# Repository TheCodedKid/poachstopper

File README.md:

<div align="center">

**Inline soft-start for Mini Cheetah motor controllers.**
Stops the power-on inrush surge that kills the input caps.

</div>

---

## Why

Cheap MIT Mini Cheetah clones have undersized input caps and no inrush limiting. Hot-plugging a charged battery, current spike into the FETs, caps die. No good, dead cheetah.

Poach Stopper splices inline on the battery lead, pre-charges through a resistor, then hands over full current. No MCU, no firmware, no buttons.

Delay time is calculated to be about `0.24` seconds, but this is due to nearly zero documentation on the knockoff motor's cap bank size, so this is more of a safety number + I think you can wait a quarter second, but if this is not the case, submit an issue.

## How it works

| Block | Parts | Job |
|-------|-------|-----|
| Soft-start bypass | G2RL-1A relay + R3 (10 Ω 5 W) | limits inrush; relay shorts it once charged |
| Delay timer | NE555 monostable mode |
| 5 V rail | LMR16006 buck, 24 V → 5 V | Powers the 555 + relay coil off the pack |
| Protection | Blade fuse F1, 1N4007 flyback D3 | Fault current + coil kickback |

<div align="center">

</div>

## Build it

JLCPCB order files are in `fab/`:

- `fab/poachstopper-gerbers.zip` — gerbers
- `fab/poachstopper-cpl.csv` — pick-and-place
- `bom/jlcpcb_bom.csv` — assembly BOM (LCSC parts)

**Hand-solder yourself** (not on PnP BOM): R3 (10 Ω 5 W), F1 fuse holder, RLA1 relay, XT60 connectors J1/J2.

Source is KiCad 10 — open `poachstopper.kicad_pro`.

## License

[MIT](LICENSE) © 2026 TheCodedKid

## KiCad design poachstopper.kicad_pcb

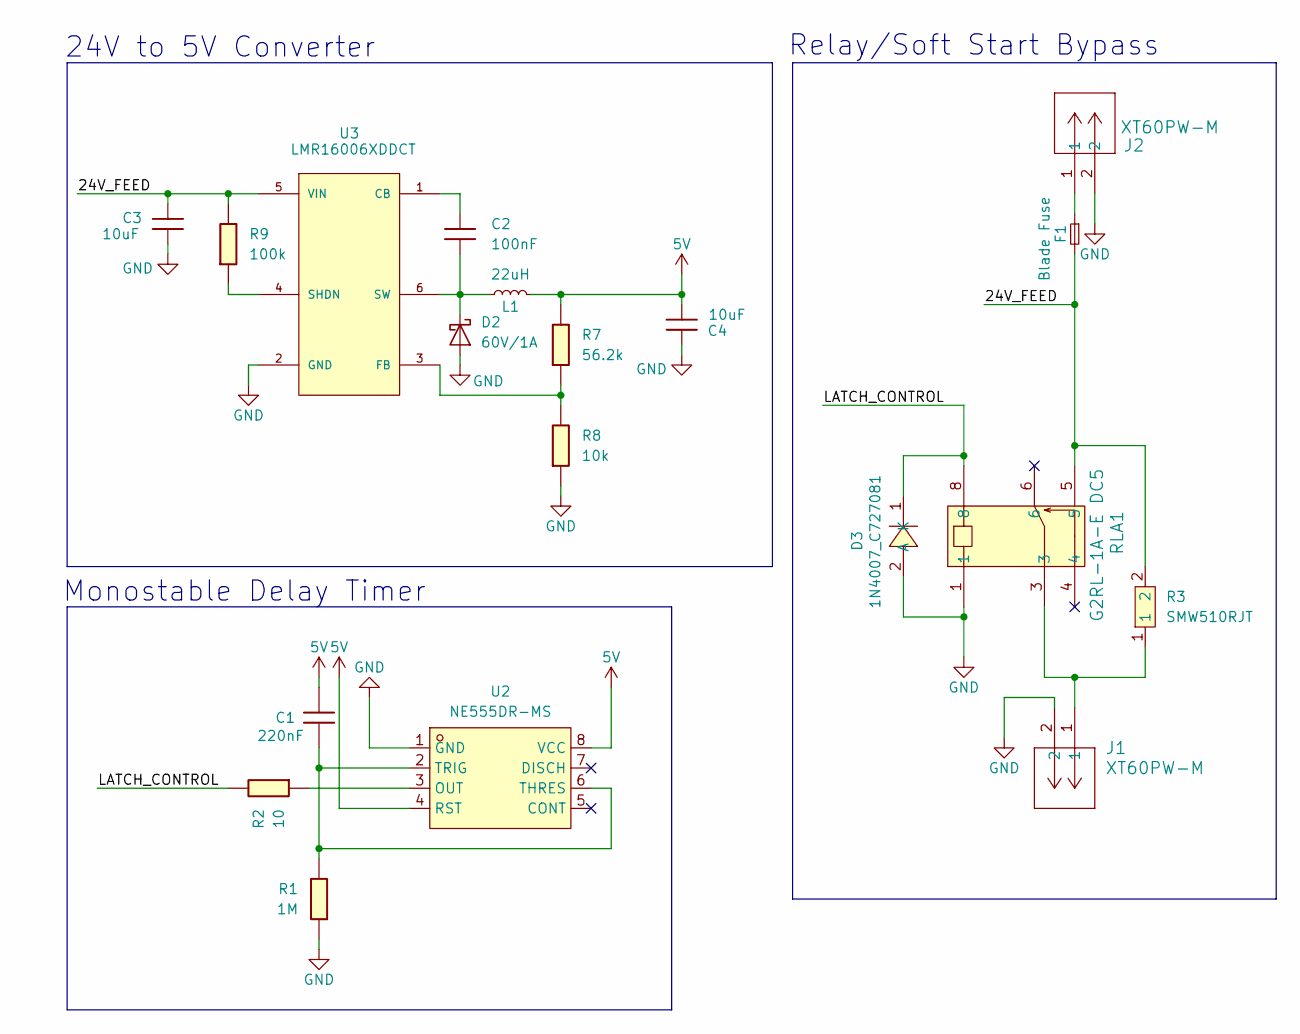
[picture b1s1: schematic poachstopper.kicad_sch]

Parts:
C1: 220nF; C_1206
C2: 100nF; C_1206
C3, C4: 10uF; C_1206
D2: 60V/1A; Diode_Schottky_0603
D3: 1N4007_C727081; SMA_L4.3-W2.5-LS5.0-RD; MPN 1N4007; LCSC Part C727081
F1: Blade Fuse; Fuseholder_Automotive
J1, J2: XT60PW-M; CONN_XT60PW-M_AMA
L1: 22uH; 0805
R1: 1M; R_1206
R2: 10; R_1206
R3: SMW510RJT; RES-SMD_L13.5-W7.3; MPN SMW510RJT; LCSC Part C2094091
R7: 56.2k; R_1206
R8: 10k; R_1206
R9: 100k; R_1206
RLA1: G2RL-1A-E DC5; RELAY_G2RL-1A-E_DC5_OMR
U2: NE555DR-MS; SOIC-8_L4.9-W3.9-P1.27-LS6.0-BL; MPN NE555DR-MS; LCSC Part C7434189
U3: LMR16006XDDCT; SOT95P280X110-6N

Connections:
5V: C1.1, C4.2, L1.2, R7.1, U2.4 (RST), U2.8 (VCC)
/24V_FEED: C3.1, F1.2, R3.2, R9.1, RLA1.5, U3.5 (VIN)
/LATCH_CONTROL: D3.1 (K), R2.1, RLA1.8
GND: C3.2, C4.1, D2.2 (A), D3.2 (A), J1.2, J2.2, R1.2, R8.2, RLA1.1, U2.1 (GND), U3.2 (GND)
unnamed: C2.2, D2.1 (K), L1.1, U3.6 (SW)
unnamed: F1.1, J2.1
unnamed: J1.1, R3.1, RLA1.3
unnamed: R2.2, U2.3 (OUT)
unnamed: C1.2, R1.1, U2.2 (TRIG), U2.6 (THRES)
unnamed: C2.1, U3.1 (CB)
unnamed: R7.2, R8.1, U3.3 (FB)
unnamed: R9.2, U3.4 (SHDN)

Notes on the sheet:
24V to 5V Converter
Relay/Soft Start Bypass
Monostable Delay Timer

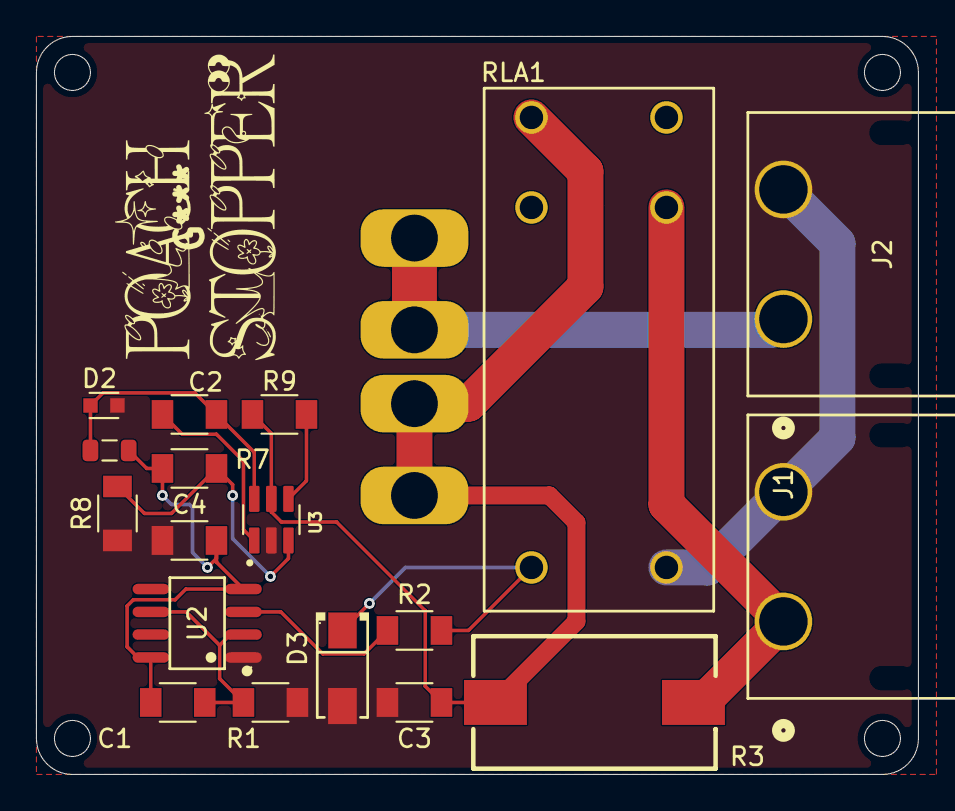
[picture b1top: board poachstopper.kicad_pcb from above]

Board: 2 copper layers, 49.0 x 41.0 mm, 19 parts (0 on the bottom side), 12 nets.

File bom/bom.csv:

Reference,Qty,Value,Footprint,MPN,Manufacturer,LCSC,LC_Stock,Chosen_Distributor,Datasheet,Validated,DNP,Notes
C1,1,220nF,1206,,,C107186,,,https://www.yageo.com/upload/media/product/productsearch/dat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,,,
D2,1,60V/1A,Diode_Schottky_0603,,,C3759853,,,https://www.digikey.com/en/products/detail/bourns-inc/CD0603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,,,
D3,1,1N4007,SMA_L4.3-W2.5-LS5.0-RD,1N4007,TWGMC(迪嘉),C727081,,,https://lcsc.com/product-detail/Diodes-General-Purpose_TWGMC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,,,SMD swap (SMA/DO-214AC) - change footprint from DO-41 before fab
F1,1,Blade Fuse,Fuseholder_Automotive,,,,,,https://www.keyelco.com/userAssets/file/M65p41.pdf,,yes,"Hand-solder, exclude from JLCPCB pick-and-place (DNP)"
"J1,J2",2,XT60PW-M,CONN_XT60PW-M_AMA,,,,,,XT60PW-M,,yes,"XT60 - order + solder separately, exclude from JLCPCB PnP (DNP)"
L1,1,22uH,0805,,,C6364733,,,https://mm.digikey.com/Volume0/opasdata/d220001/medias/docus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,,,
R1,1,1M,1206,,,C17927,,,,,,
R2,1,10,1206,,,C17903,,,,,,
R3,1,10,RES-SMD_L13.5-W7.3,SMW510RJT,TE Connectivity(泰科电子),C2094091,,,https://www.lcsc.com/datasheet/C2094091.pdf,,,10R 5W SMD - change footprint from 3550 to RES-SMD_L13.5-W7.3 before fab
R7,1,56.2k,1206,,,C2999490,,,,,,
R8,1,10k,1206,,,C17902,,,,,,
R9,1,100k,1206,,,C17900,,,,,,
RLA1,1,G2RL-1A-E DC5,RELAY_G2RL-1A-E_DC5_OMR,,,,,,G2RL-1A-E DC5,,yes,"Relay - order + solder separately, exclude from JLCPCB PnP (DNP)"
U2,1,NE555DR-MS,SOIC-8_L4.9-W3.9-P1.27-LS6.0-BL,NE555DR-MS,MSKSEMI(美森科),C7434189,,,https://www.lcsc.com/datasheet/C7434189.pdf,,,
U3,1,LMR16006XDDCT,SOT95P280X110-6N,,,C87080,,,,,,

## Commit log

2026-06-22 init
2026-06-22 draft created
2026-06-22 going running
2026-06-29 circuit cleanup, functionality finalized, BOM
2026-06-30 v0.1.0
2026-06-30 fixed image
2026-06-30 removed slop documentation
2026-06-30 photo update
